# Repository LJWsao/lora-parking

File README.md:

# Overview
This project contains the files for the LoRa parking project.

## Technical Description

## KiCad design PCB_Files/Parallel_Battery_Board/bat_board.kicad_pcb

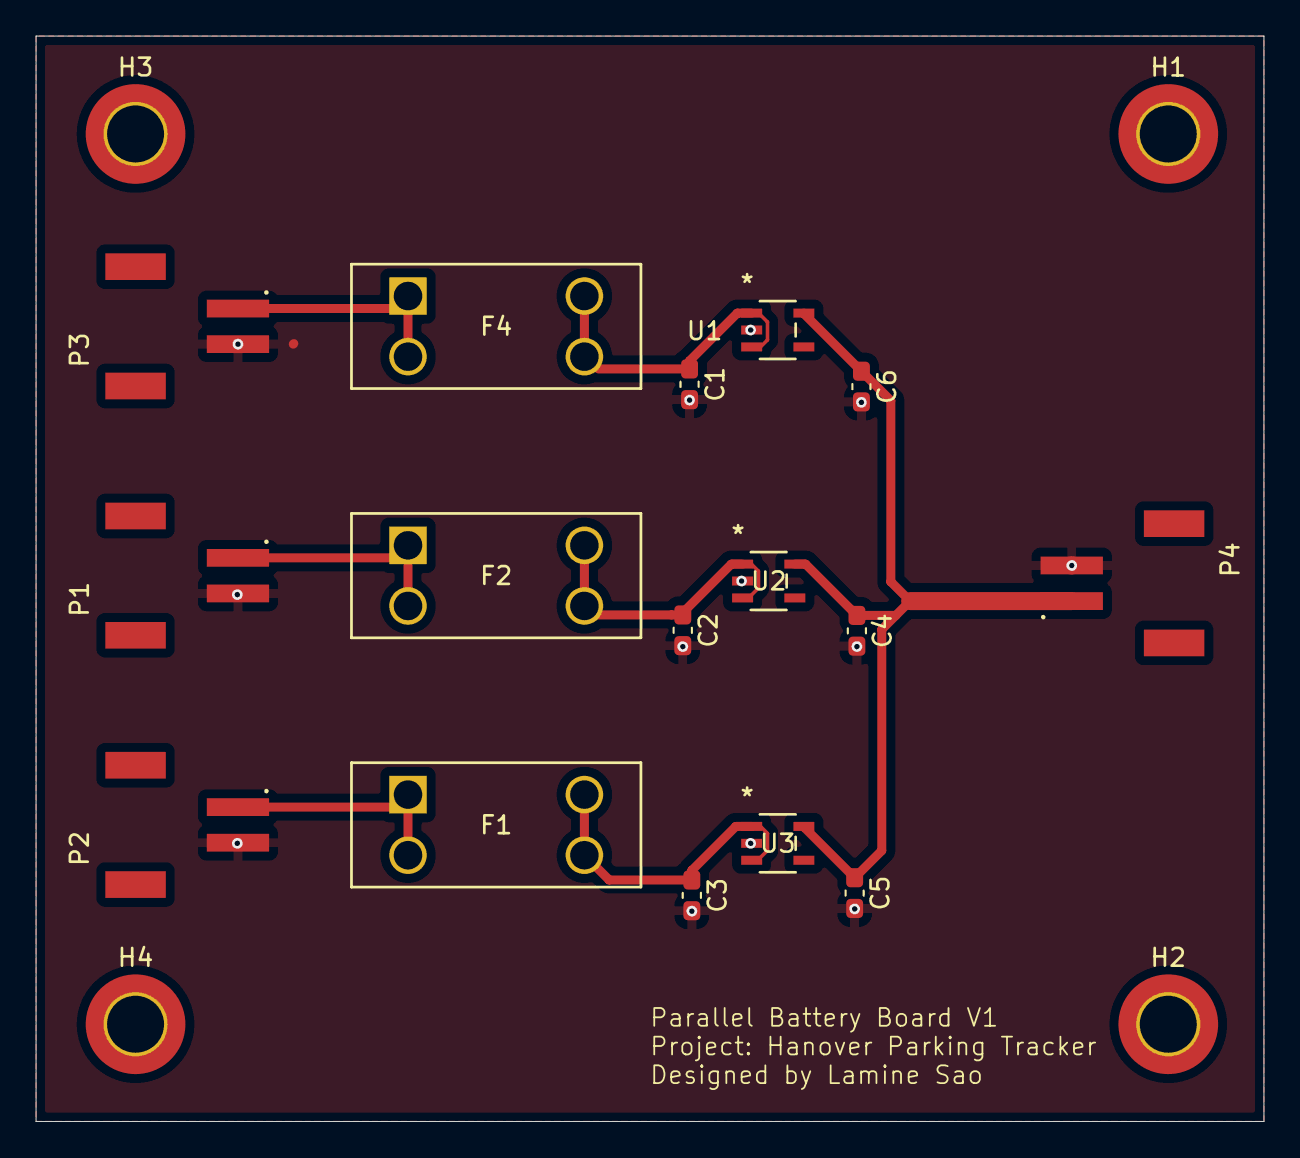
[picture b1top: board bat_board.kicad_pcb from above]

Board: 2 copper layers, 69.0 x 61.0 mm, 20 parts (0 on the bottom side), 8 nets.

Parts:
C1, C2, C3, C4, C5, C6: 0.33 uF; C_0603_1608Metric_Pad1.08x0.95mm_HandSolder
F1, F2, F4: 2A; 3568_KEY_Mini_Fuse_Mount
H1, H2, H3, H4: MountingHole; MountingHole_3.2mm_M3_DIN965_Pad_TopBottom
P1, P2, P3, P4: S2B-PH-SM4-TB; JST_S2B-PH-SM4-TB
U1, U2, U3: MAX40200AUK+T; 21-0057F_MXM-M

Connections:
GND: C1.2, C2.2, C3.2, C4.2, C5.2, C6.2, H1.1, H2.1, H3.1, H4.1, P1.2 (2_(-)), P2.2 (2_(-)), P3.2 (2_(-)), P4.2 (2_(-)), U1.2 (GND), U2.2 (GND), U3.2 (GND)
unnamed: F2.1, F2.2, P1.1 (1_(+))
unnamed: F1.1, F1.2, P2.1 (1_(+))
unnamed: F4.1, F4.2, P3.1 (1_(+))
unnamed: C4.1, C5.1, C6.1, P4.1 (1_(+)), U1.5 (OUT), U2.5 (OUT), U3.5 (OUT)
unnamed: C1.1, F4.3, F4.4, U1.1 (VDD), U1.3 (EN)
unnamed: C3.1, F1.3, F1.4, U3.1 (VDD), U3.3 (EN)
unnamed: C2.20, F2.3, F2.4, U2.1 (VDD), U2.3 (EN)

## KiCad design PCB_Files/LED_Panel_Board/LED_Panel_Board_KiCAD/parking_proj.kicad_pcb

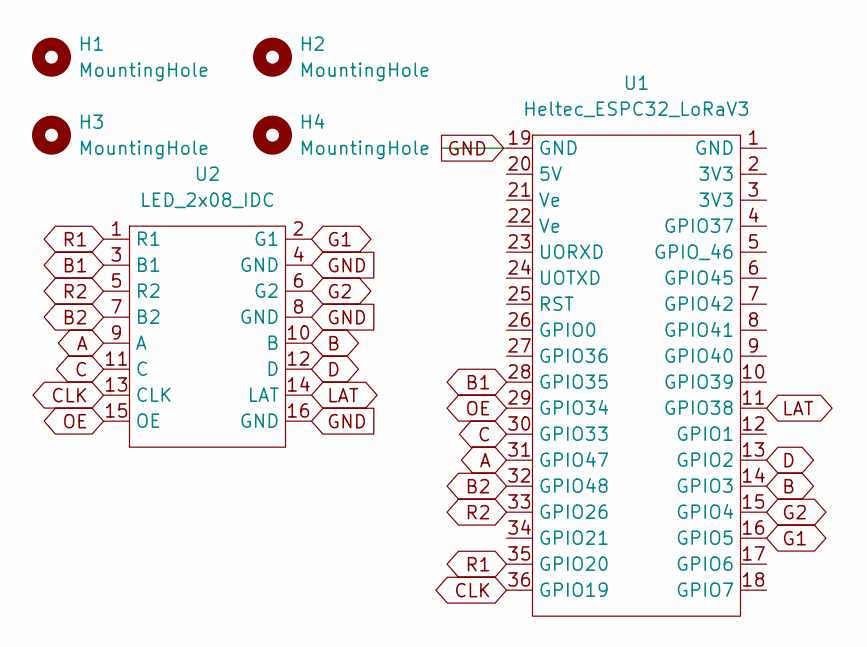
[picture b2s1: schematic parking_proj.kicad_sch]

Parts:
H1, H2, H3, H4: MountingHole; MountingHole_3.2mm_M3_DIN965_Pad
U1: Heltec_ESPC32_LoRaV3; MODULE_WIFI_KIT_32__V3_
U2: LED_2x08_IDC; IDC-Header_2x08_P2.54mm_Vertical

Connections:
A: U1.31 (GPIO47), U2.9 (A)
B: U1.14 (GPIO3), U2.10 (B)
B1: U1.28 (GPIO35), U2.3 (B1)
B2: U1.32 (GPIO48), U2.7 (B2)
C: U1.30 (GPIO33), U2.11 (C)
CLK: U1.36 (GPIO19), U2.13 (CLK)
D: U1.13 (GPIO2), U2.12 (D)
G1: U1.16 (GPIO5), U2.2 (G1)
G2: U1.15 (GPIO4), U2.6 (G2)
GND: U1.19 (GND), U2.4 (GND), U2.8 (GND), U2.16 (GND)
LAT: U1.11 (GPIO38), U2.14 (LAT)
OE: U1.29 (GPIO34), U2.15 (OE)
R1: U1.35 (GPIO20), U2.1 (R1)
R2: U1.33 (GPIO26), U2.5 (R2)

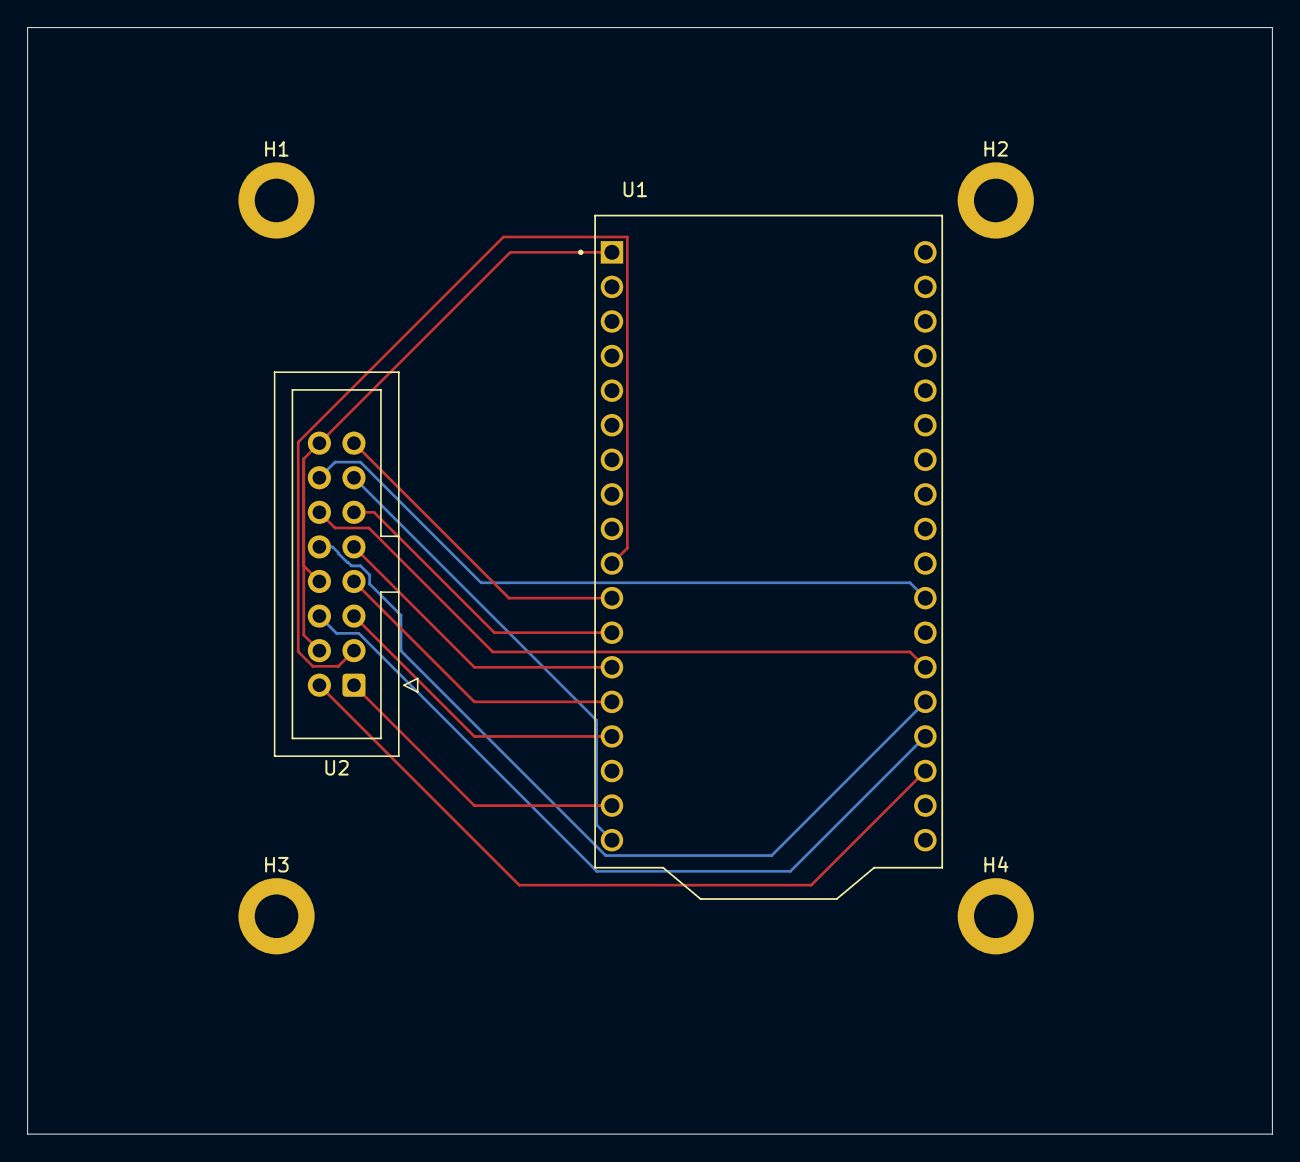
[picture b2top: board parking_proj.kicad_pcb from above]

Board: 2 copper layers, 91.4 x 81.3 mm, 6 parts (0 on the bottom side), 14 nets.

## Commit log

2025-08-18 Rename BLE_server_counter_display.ino to ESP32/BLE_server_counter_display.ino
2025-08-18 Rename car_display_LoRa.ino to ESP32/car_display_LoRa.ino
2025-08-18 Rename carEnteredLoRa.ino to car_entered_LoRa.ino
2025-08-18 Rename inc_carleftLoRa.ino.ino to car_ext_LoRa.ino.ino
2025-08-18 Rename car_ext_LoRa.ino.ino to car_exit_LoRa.ino.ino
2025-08-19 Revert recv_only_display.ino
2025-08-19 Fixed inability to send full update with onTxDone interrupt handling
2025-08-29 Create recv_only_display_LEDMatrix
2025-12-31 Update recv_only_display_LEDMatrix
    Changed GPIO to stop top half of LED matrix from being blue
2026-01-03 Update app_v2.html
    New version with keypad for kiosk mode
2026-01-28 Added IMU and distance sensor switching
2026-01-28 Rename car_enter_v2.ino to car_exit_v2.ino
2026-01-28 Rename ble_v3.ino to ble_heltec_v3.ino
2026-01-28 IMU + sensor switching: Create car_entered_LoRa_v2.ino
2026-01-28 Added SDA and SCL definitions car_entered_LoRa_v2.ino
2026-01-28 Update car_exit_v2.ino with SDA and SCL definitions
2026-02-01 IMU working, Distance not working: car_entered_LoRa_v2.ino
    Can read from IMU now. Mode switching works. However, distance sensor mode does not work. The state tracking code got messed up so I will need to integrate the previous logic.
2026-02-04 Rename car_entered_LoRa_v2.ino to car_exit_LoRa_v2.ino
2026-02-05 Updated FSM_car_enter.ino
    OLED messages now update properly. Seems to be working. Still have to add IMU support.
2026-02-06 IMU Logic FSM_car_enter.ino
    Added IMU logic. Better triggering logic based on absolute position. TODO: Make the same changes for the distance sensor to remove the time based shenanigans.
2026-05-07 Fully working set of files
    Web app now has scheduling for switching sensor modes.
    Fixed over the air sensor mode switching issue - was a state machine problem within
2026-05-07 Rename app_v4.html to web_app/app_v4.html
2026-05-08 Parallel Board PCB Files Component datasheets, footprints, symbols, 3d models
2026-05-08 LED Panel Board KiCAD Design so far (no voltage regulator yet)
2026-05-08 minor kicad edits
2026-05-08 v1 of parallel charging board complete
2026-05-08 OCD Parallel board changes
2026-05-08 labeled PCB with name
2026-05-08 final parallel board PCB changes for the night
